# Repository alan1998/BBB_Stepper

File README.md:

# BBB_Stepper
Really simple 3 axis Pololu to beagle bone black

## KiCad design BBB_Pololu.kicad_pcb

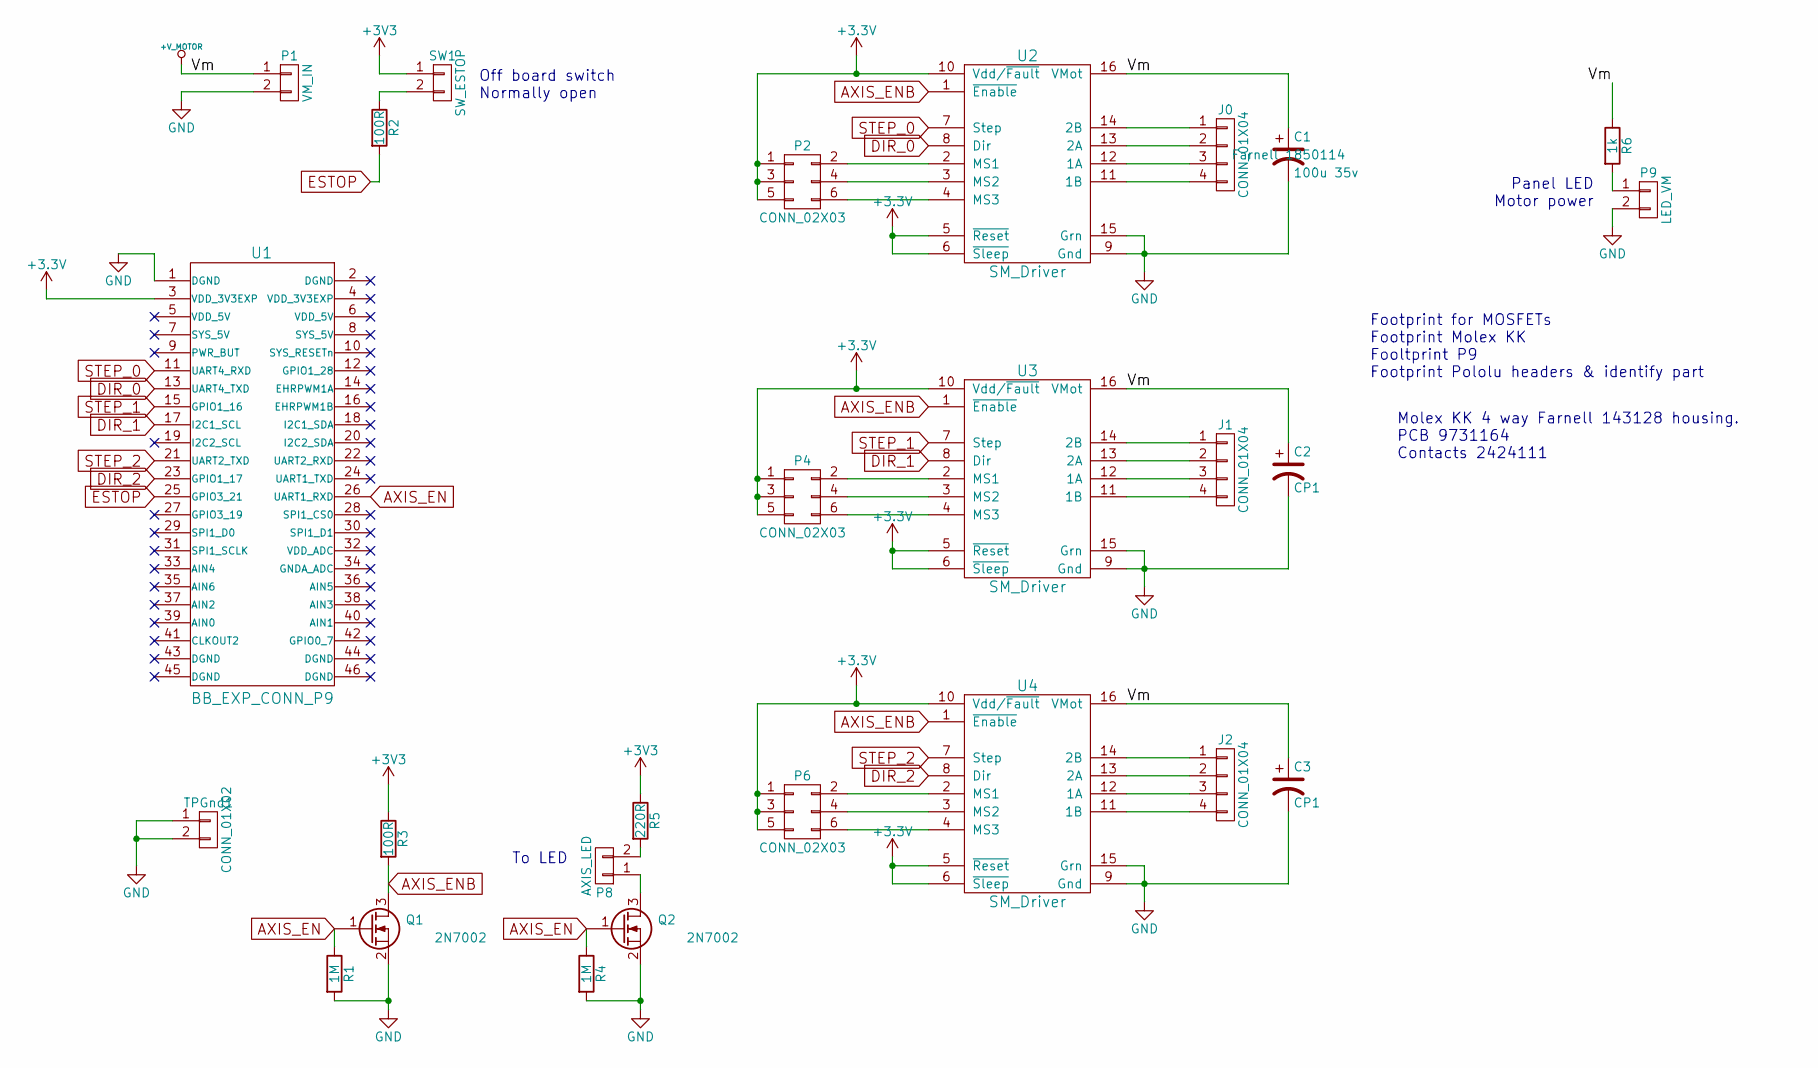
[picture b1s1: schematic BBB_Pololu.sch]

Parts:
C1: 100u 35v; c_elec_6.3x7.7
C2, C3: CP1; c_elec_6.3x7.7
J0, J1, J2: CONN_01X04; Molex_KK_6410-04
P1: VM_IN; Molex_KK_6410-02
P2, P4, P6: CONN_02X03; Pin_Header_Straight_2x03
P8: AXIS_LED; Pin_Header_Straight_1x02
P9: LED_VM; Pin_Header_Straight_1x02
Q1, Q2: 2N7002; SOT-23_Handsoldering
R1, R4: 1M; R_0805_HandSoldering
R2, R3: 100R; R_0805_HandSoldering
R5: 220R; R_0805_HandSoldering
R6: 1k; R_0805_HandSoldering
SW1: SW_ESTOP; Molex_KK_6410-02
TPGnd1: CONN_01X02; Pin_Header_Straight_1x02
U1: BB_EXP_CONN_P9; BBB_P8P9_PinHeader
U2, U3, U4: SM_Driver; POLOLU

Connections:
/Vm: C1.1, C2.1, C3.1, P1.1, R6.1, U2.16 (VMot), U3.16 (VMot), U4.16 (VMot)
AXIS_EN: Q1.1 (G), Q2.1 (G), R1.1, R4.1, U1.26 (UART1_RXD)
AXIS_ENB: Q1.3 (D), R3.2, U2.1 (~Enable), U3.1 (~Enable), U4.1 (~Enable)
DIR_0: U1.13 (UART4_TXD), U2.8 (Dir)
DIR_1: U1.17 (I2C1_SCL), U3.8 (Dir)
DIR_2: U1.23 (GPIO1_17), U4.8 (Dir)
ESTOP: R2.2, U1.25 (GPIO3_21)
GND: C1.2, C2.2, C3.2, P1.2, P9.2, Q1.2 (S), Q2.2 (S), R1.2, R4.2, TPGnd1.1, TPGnd1.2, U1.1 (DGND), U2.9 (Gnd), U2.15 (Grn), U3.9 (Gnd), U3.15 (Grn), U4.9 (Gnd), U4.15 (Grn); also elsewhere on the board
unnamed: J0.1, U2.14 (2B)
unnamed: J0.2, U2.13 (2A)
unnamed: J0.3, U2.12 (1A)
unnamed: J0.4, U2.11 (1B)
unnamed: J1.1, U3.14 (2B)
unnamed: J1.2, U3.13 (2A)
unnamed: J1.3, U3.12 (1A)
unnamed: J1.4, U3.11 (1B)
unnamed: J2.1, U4.14 (2B)
unnamed: J2.2, U4.13 (2A)
unnamed: J2.3, U4.12 (1A)
unnamed: J2.4, U4.11 (1B)
unnamed: P2.2, U2.2 (MS1)
unnamed: P2.4, U2.3 (MS2)
unnamed: P2.6, U2.4 (MS3)
unnamed: P4.2, U3.2 (MS1)
unnamed: P4.4, U3.3 (MS2)
unnamed: P4.6, U3.4 (MS3)
unnamed: P6.2, U4.2 (MS1)
unnamed: P6.4, U4.3 (MS2)
unnamed: P6.6, U4.4 (MS3)
unnamed: P8.1, Q2.3 (D)
unnamed: P8.2, R5.2
unnamed: P9.1, R6.2
unnamed: R2.1, SW1.2
STEP_0: U1.11 (UART4_RXD), U2.7 (Step)
STEP_1: U1.15 (GPIO1_16), U3.7 (Step)
STEP_2: U1.21 (UART2_TXD), U4.7 (Step)

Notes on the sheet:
Off board switch Normally open
To LED
Panel LED Motor power
Footprint for MOSFETs Footprint Molex KK Fooltprint P9 Footprint Pololu headers & identify part
Molex KK 4 way Farnell 143128 housing. PCB 9731164 Contacts 2424111

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
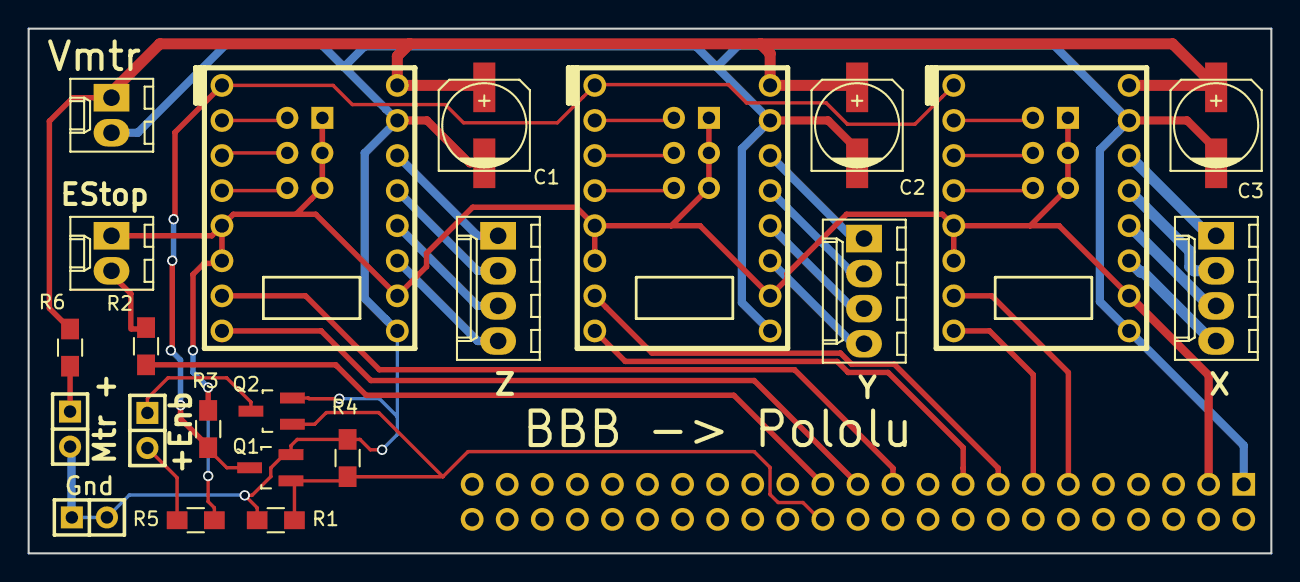
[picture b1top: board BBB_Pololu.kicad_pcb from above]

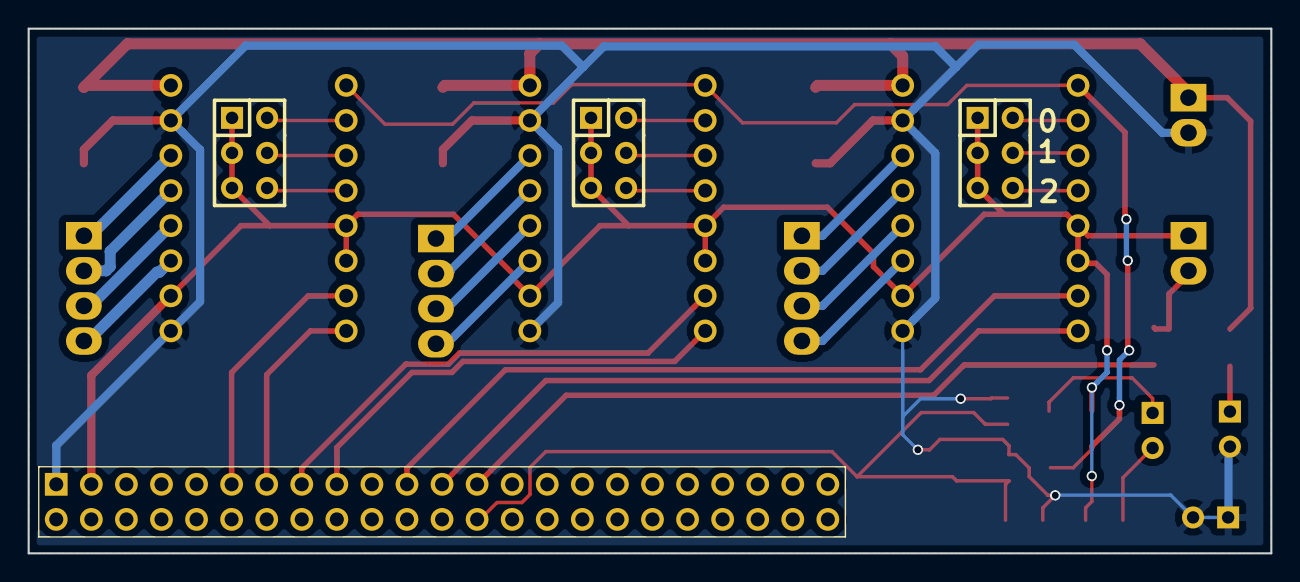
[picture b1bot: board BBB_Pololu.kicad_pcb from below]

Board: 2 copper layers, 90.0 x 38.0 mm, 26 parts (3 on the bottom side), 37 nets.

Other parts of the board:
Gnd: CONN_01X02; Pin_Header_Straight_1x02

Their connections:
GND: Gnd.1, Gnd.2; also elsewhere on the board

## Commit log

2016-06-27 Add files
2016-06-27 Routed but checks to be done
2016-06-27 Silk not finished
2016-06-28 As sent for manufacture
